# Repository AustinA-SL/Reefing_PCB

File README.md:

# Electronic Parachute Reefing PCB (Reef V3)

KiCad 10 project for the electronic parachute reefing controller.

- `V2_solenoid_removed/` is the V2 board (solenoid circuit removed, all parts on the top side). The original pre-V2 design is not tracked here.
- `libs/UL_Parts.pretty/` is a snapshot of the custom footprint library. The project's `fp-lib-table` still points at `C:/Users/austi/Documents/KiCad/10.0/footprints/UL_Parts.pretty`; footprints are also embedded in the `.kicad_pcb`, so the board opens without the library.

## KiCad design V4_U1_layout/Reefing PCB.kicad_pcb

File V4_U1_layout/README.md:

# Reef V3 controller — V4_U1_layout

Parachute reefing controller built around a Teensy 4.1. Four-layer board; every part is on the top side.

## Review files

| File | What it is |
|---|---|
| [plot/Reefing PCB schematic.pdf](plot/Reefing%20PCB%20schematic.pdf) | Full schematic |
| [docs/board_layers.pdf](docs/board_layers.pdf) | One page each: F.Cu, In1.Cu, In2.Cu, B.Cu, F.Silkscreen (with board outline) |
| [docs/board_top.png](docs/board_top.png) | 3D render, top side |
| [plot/](plot/) | Gerbers (`.gbr`, `.gbrjob`) and Excellon drill file (`.drl`) |

## Stackup

| Layer | Use |
|---|---|
| F.Cu | Components, signals, local power pours |
| In1.Cu | Solid GNDA plane |
| In2.Cu | Power: VIN and 12V pours, 24V and 3V3 routing |
| B.Cu | GNDA pour |

## Main parts

| Ref | Part | Function |
|---|---|---|
| U1 | TPS551892-Q1 | 12V buck-boost |
| U2 | TPS55340 | 24V boost |
| U3 | DRV8243-Q1 | Motor driver |
| U6 | LMR16006 | 5V buck |
| U8 / U9 | SN74LVC04 / SN74LVC10 | Interlock logic |
| IC1 | Teensy 4.1 | Controller |

## Net class track widths

| Class | Width |
|---|---|
| Power_4A | 1.5 mm |
| Motor | 1.0 mm |
| Power | 0.5 mm |
| Default | 0.2 mm |

## Fab notes

- Minimum drill is 0.2 mm (TI thermal-via patterns under U2 and U3).
- The U3 VM vias are in-pad and should be filled.
- The Teensy 4.1 footprint has its inner pads removed on purpose. Don't update that footprint from the library.
- DRC is clean as of 2026-11-16.

## Opening the design

1. Clone this repo.
2. Open `V4_U1_layout/Reefing PCB.kicad_pro` in KiCad 10.

The `UL_Parts` footprint library comes from `libs/UL_Parts.pretty` in this repo. All other footprints are stored inside the board file, so it opens and passes DRC without extra libraries.

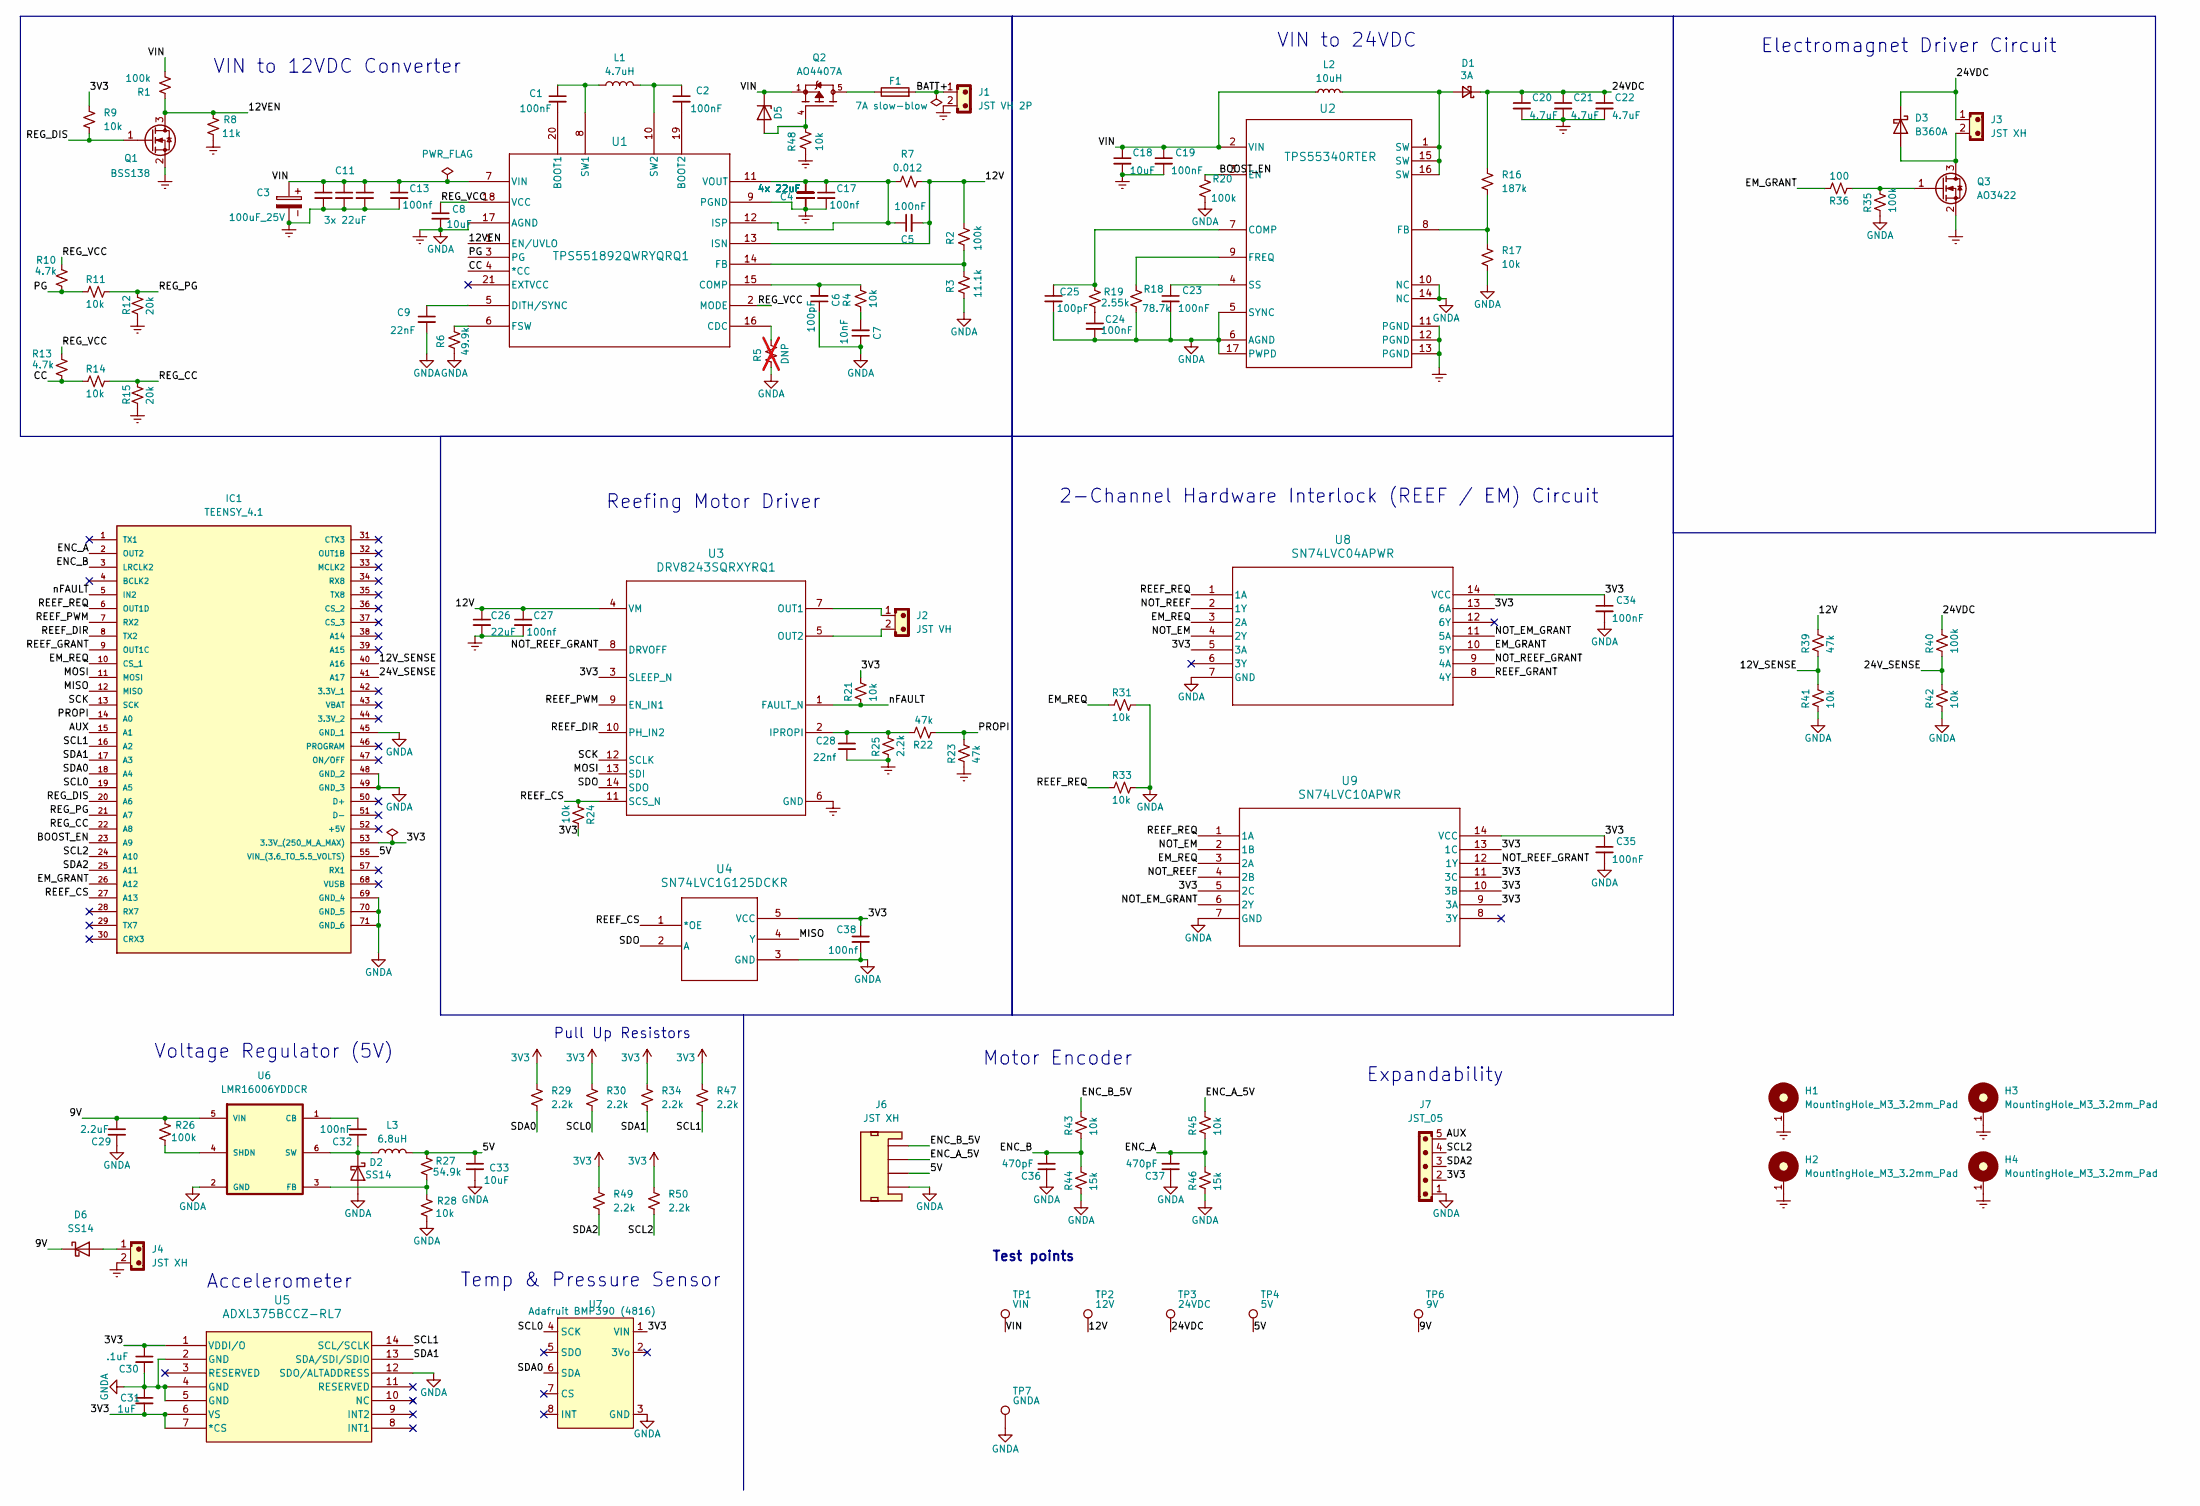
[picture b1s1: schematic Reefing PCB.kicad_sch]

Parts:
C1, C2: 100nF; C_0603_1608Metric; Voltage 10V; Tolerance 20%
C3: 100uF_25V; CP_Radial_D6.3mm_P2.50mm
C4, C14, C15, C16: 4x 22uF; C_1210_3225Metric; Voltage 25V; Tolerance 20%
C5, C19, C23, C24, C34, C35: 100nF; C_0603_1608Metric; Voltage 25V; Tolerance 20%
C6: 100pF; C_0603_1608Metric; Voltage 10V; Tolerance 20%
C7: 10nF; C_0603_1608Metric; Voltage 10V; Tolerance 20%
C8: 10uF; C_1206_3216Metric; Voltage 16V; Tolerance 20%
C9: 22nF; C_0603_1608Metric; Voltage 10V; Tolerance 20%
C10, C11, C12: 3x 22uF; C_1210_3225Metric; Voltage 50V; Tolerance 20%
C13, C17, C27: 100nf; C_0603_1608Metric; Voltage 25V; Tolerance 20%
C18: 10uF; C_1210_3225Metric; Voltage 50V; Tolerance 20%
C20, C21, C22: 4.7uF; C_1210_3225Metric; Voltage 50V; Tolerance 20%
C25: 100pF; C_0603_1608Metric; Voltage 25V; Tolerance 20%
C26: 22uF; C_1210_3225Metric; Voltage 50V; Tolerance 20%
C28: 22nf; C_0603_1608Metric; Voltage 10V; Tolerance 20%
C29: 2.2uF; C_0805_2012Metric
C30: .1uF; C_0603_1608Metric
C31: 1uF; C_0603_1608Metric
C32: 100nF; C_0603_1608Metric
C33: 10uF; C_0805_2012Metric
C36, C37: 470pF; C_0603_1608Metric
C38: 100nf; C_0603_1608Metric; Voltage 10V; Tolerance 20%
D1: SK34A; D_SMA
D2, D6: SS14; D_SMA
D3: B360A; D_SMA
D5: BZT52C15; D_SOD-123F
F1: 7A slow-blow; Fuse_Littelfuse-NANO2-451_453
H1, H2, H3, H4: MountingHole_M3_3.2mm_Pad; MountingHole_3.2mm_Pad
IC1: TEENSY_4.1; TEENSY41; Manufacturer_Part_Number TEENSY 4.1
J1: JST VH 2P; JST_VH_B2P-VH_1x02_P3.96mm_Vertical
J2: JST VH; JST_VH_B2P-VH_1x02_P3.96mm_Vertical
J3: JST XH; JST_GH_SM02B-GHS-TB_1x02-1MP_P1.25mm_Horizontal
J4: JST XH; JST_XH_B2B-XH-A_1x02_P2.50mm_Vertical
J6: JST XH; JST_GH_SM04B-GHS-TB_1x04-1MP_P1.25mm_Horizontal
J7: JST_05; JST_GH_SM05B-GHS-TB_1x05-1MP_P1.25mm_Horizontal
L1: 4.7uH; L_Coilcraft_XAL6060-XXX
L2: 10uH; L_Coilcraft_XAL4040-XXX
L3: 6.8uH; L_Coilcraft_LPS4018
Q1: BSS138; SOT-23
Q2: AO4407A; SOIC127P600X175-8N; PARTREV I
Q3: AO3422; SOT-23
R1, R2, R20, R26, R35, R40: 100k; R_0603_1608Metric
R3: 11.1k; R_0603_1608Metric
R4, R9, R11, R14, R17, R21, R24, R28, R31, R33, R41, R42, R43, R45, R48: 10k; R_0603_1608Metric
R5: DNP; R_0603_1608Metric; not fitted
R6: 49.9k; R_0603_1608Metric
R7: 0.012; R_2512_6332Metric
R8: 11k; R_0603_1608Metric
R10, R13: 4.7k; R_0603_1608Metric
R12, R15: 20k; R_0603_1608Metric
R16: 187k; R_0603_1608Metric
R18: 78.7k; R_0603_1608Metric
R19: 2.55k; R_0603_1608Metric
R22, R23, R39: 47k; R_0603_1608Metric
R25, R29, R30, R34, R47, R49, R50: 2.2k; R_0603_1608Metric
R27: 54.9k; R_0603_1608Metric
R36: 100; R_0603_1608Metric
R44, R46: 15k; R_0603_1608Metric
TP1: VIN; TestPoint_Pad_D1.5mm
TP2: 12V; TestPoint_Pad_D1.5mm
TP3: 24VDC; TestPoint_Pad_D1.5mm
TP4: 5V; TestPoint_Pad_D1.5mm
TP6: 9V; TestPoint_Pad_D1.5mm
TP7: GNDA; TestPoint_Pad_D1.5mm
U1: TPS551892QWRYQRQ1; VQFN21_RYQ_TEX
U2: TPS55340RTER; RTE0016C
U3: DRV8243SQRXYRQ1; RXY0014A-MFG
U4: SN74LVC1G125DCKR; DCK5
U5: ADXL375BCCZ-RL7; LGA_CC-14-1_ADI
U6: LMR16006YDDCR; SOT95P280X110-6N
U7: Adafruit BMP390 (4816); PinSocket_1x08_P2.54mm_Vertical
U8: SN74LVC04APWR; PW14
U9: SN74LVC10APWR; PW14

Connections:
3V3: C30.1, C31.2, C34.1, C35.1, C38.1, IC1.53 (3.3V_(250_M_A_MAX)), J7.2, R9.2, R21.1, R24.1, R29.2, R30.2, R34.2, R47.2, R49.2, R50.2, U3.3 (SLEEP_N), U4.5 (VCC), U5.1 (VDDI/O), U5.6 (VS), U5.7 (*CS), U7.1 (VIN), U8.5 (3A), U8.13 (6A), U8.14 (VCC), U9.5 (2C), U9.9 (3A), U9.10 (3B), U9.11 (3C), U9.13 (1C), U9.14 (VCC)
/5V: C33.1, IC1.55 (VIN_(3.6_TO_5.5_VOLTS)), J6.2, L3.2, R27.2, TP4.1 (1_1)
/9V: C29.1, D6.1 (K), R26.2, TP6.1 (1_1), U6.5 (VIN)
/12V: C5.2, C26.1, C27.1, R2.2, R7.2, R39.1, TP2.1 (1_1), U1.13 (ISN), U3.4 (VM)
/12VEN: Q1.3 (D), R1.2, R8.1, U1.1 (EN/UVLO)
/12V_SENSE: IC1.40 (A16), R39.2, R41.1
/24VDC: C20.1, C21.1, C22.1, D1.1 (K), D3.1 (K), J3.1, R16.2, R40.1, TP3.1 (1_1)
/24V_SENSE: IC1.41 (A17), R40.2, R42.1
/AUX: IC1.15 (A1), J7.5
/BATT+: F1.2, J1.1
/BOOST_EN: IC1.23 (A9), R20.2, U2.3 (EN)
/CC: R13.1, R14.2, U1.4 (*CC)
/EM_GRANT: IC1.26 (A12), R36.1, U8.10 (5Y)
/EM_REQ: IC1.10 (CS_1), R31.2, U8.3 (2A), U9.3 (2A)
/ENC_A: C37.1, IC1.2 (OUT2), R45.2, R46.1
/ENC_A_5V: J6.3, R45.1
/ENC_B: C36.1, IC1.3 (LRCLK2), R43.2, R44.1
/ENC_B_5V: J6.4, R43.1
/MISO: IC1.12 (MISO), U4.4 (Y)
/MOSI: IC1.11 (MOSI), U3.13 (SDI)
/NOT_EM: U8.4 (2Y), U9.2 (1B)
/NOT_EM_GRANT: U8.11 (5A), U9.6 (2Y)
/NOT_REEF: U8.2 (1Y), U9.4 (2B)
/NOT_REEF_GRANT: U3.8 (DRVOFF), U8.9 (4A), U9.12 (1Y)
/PG: R10.1, R11.2, U1.3 (PG)
/PROPI: IC1.14 (A0), R22.2, R23.1
/REEF_CS: IC1.27 (A13), R24.2, U3.11 (SCS_N), U4.1 (*OE)
/REEF_DIR: IC1.8 (TX2), U3.10 (PH_IN2)
/REEF_GRANT: IC1.9 (OUT1C), U8.8 (4Y)
/REEF_PWM: IC1.7 (RX2), U3.9 (EN_IN1)
/REEF_REQ: IC1.6 (OUT1D), R33.2, U8.1 (1A), U9.1 (1A)
/REG_CC: IC1.22 (A8), R14.1, R15.2
/REG_DIS: IC1.20 (A6), Q1.1 (G), R9.1
/REG_PG: IC1.21 (A7), R11.1, R12.2
/REG_VCC: C8.1, R10.2, R13.2, U1.2 (MODE), U1.18 (VCC)
/SCK: IC1.13 (SCK), U3.12 (SCLK)
/SCL0: IC1.19 (A5), R30.1, U7.4 (SCK)
/SCL1: IC1.16 (A2), R47.1, U5.14 (SCL/SCLK)
/SCL2: IC1.24 (A10), J7.4, R50.1
/SDA0: IC1.18 (A4), R29.1, U7.6 (SDA)
/SDA1: IC1.17 (A3), R34.1, U5.13 (SDA/SDI/SDIO)
/SDA2: IC1.25 (A11), J7.3, R49.1
/SDO: U3.14 (SDO), U4.2 (A)
/VIN: C3.1, C10.1, C11.1, C12.1, C13.1, C18.1, C19.1, D5.1 (K), L2.1, Q2.1, Q2.2, Q2.3, R1.1, TP1.1 (1_1), U1.7 (VIN), U2.2 (VIN)
/nFAULT: IC1.5 (IN2), R21.2, U3.1 (FAULT_N)
GNDA: C3.2, C4.2, C6.1, C7.1, C8.2, C9.2, C10.2, C11.2, C12.2, C13.2, C14.2, C15.2, C16.2, C17.2, C18.2, C19.2, C20.2, C21.2, C22.2, C23.2, C24.2, C25.2, C26.2, C27.2, C28.2, C29.2, C30.2, C31.1, C33.2, C34.2, C35.2, C36.2, C37.2, C38.2, D2.2 (A), H1.1, H2.1, H3.1, H4.1, IC1.45 (GND_1), IC1.48 (GND_2), IC1.49 (GND_3), IC1.69 (GND_4), IC1.70 (GND_5), IC1.71 (GND_6), J1.2, J4.2, J6.1, J7.1, Q1.2 (S), Q3.2 (S), R3.1, R5.1, R6.1, R8.2, R12.1, R15.1, R17.1, R18.1, R20.1, R23.2, R25.2, R28.1, R31.1, R33.1, R35.2, R41.2, R42.2, R44.2, R46.2, R48.1, TP7.1 (1_1), U1.9 (PGND), U1.17 (AGND), U2.5 (SYNC), U2.6 (AGND), U2.10 (NC), U2.11 (PGND), U2.12 (PGND), U2.13 (PGND), U2.14 (NC), U2.17 (PWPD), U3.6 (GND), U4.3 (GND), U5.2 (GND), U5.4 (GND), U5.5 (GND), U5.12 (SDO/ALTADDRESS), U6.2 (GND), U7.3 (GND), U8.7 (GND), U9.7 (GND)
unnamed: C7.2, R4.1
unnamed: C24.1, R19.1
unnamed: D1.2 (A), L2.2, U2.1 (SW), U2.15 (SW), U2.16 (SW)
unnamed: C32.2, D2.1 (K), L3.1, U6.6 (SW)
unnamed: D3.2 (A), J3.2, Q3.3 (D)
unnamed: D5.2 (A), Q2.4, R48.2
unnamed: D6.2 (A), J4.1
unnamed: F1.1, Q2.5, Q2.6, Q2.7, Q2.8
unnamed: Q3.1 (G), R35.1, R36.2
unnamed: C1.2, U1.20 (BOOT1)
unnamed: C2.2, U1.19 (BOOT2)
unnamed: R5.2, U1.16 (CDC)
unnamed: C6.2, R4.2, U1.15 (COMP)
unnamed: C9.1, U1.5 (DITH/SYNC)
unnamed: R2.1, R3.2, U1.14 (FB)
unnamed: R6.2, U1.6 (FSW)
unnamed: C4.1, C5.1, C14.1, C15.1, C16.1, C17.1, R7.1, U1.11 (VOUT), U1.12 (ISP)
unnamed: C1.1, L1.1, U1.8 (SW1)
unnamed: C2.1, L1.2, U1.10 (SW2)
unnamed: C25.1, R19.2, U2.7 (COMP)
unnamed: R16.1, R17.2, U2.8 (FB)
unnamed: R18.2, U2.9 (FREQ)
unnamed: C23.1, U2.4 (SS)
unnamed: C28.1, R22.1, R25.1, U3.2 (IPROPI)
unnamed: J2.1, U3.7 (OUT1)
unnamed: J2.2, U3.5 (OUT2)
unnamed: C32.1, U6.1 (CB)
unnamed: R27.1, R28.2, U6.3 (FB)
unnamed: R26.1, U6.4 (SHDN)

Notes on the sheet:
Pull Up Resistors
Reefing Motor Driver
VIN to 12VDC Converter
Expandability
Temp & Pressure Sensor
Electromagnet Driver Circuit
2-Channel Hardware Interlock (REEF / EM) Circuit
Accelerometer
VIN to 24VDC
Test points
Motor Encoder
Voltage Regulator (5V)

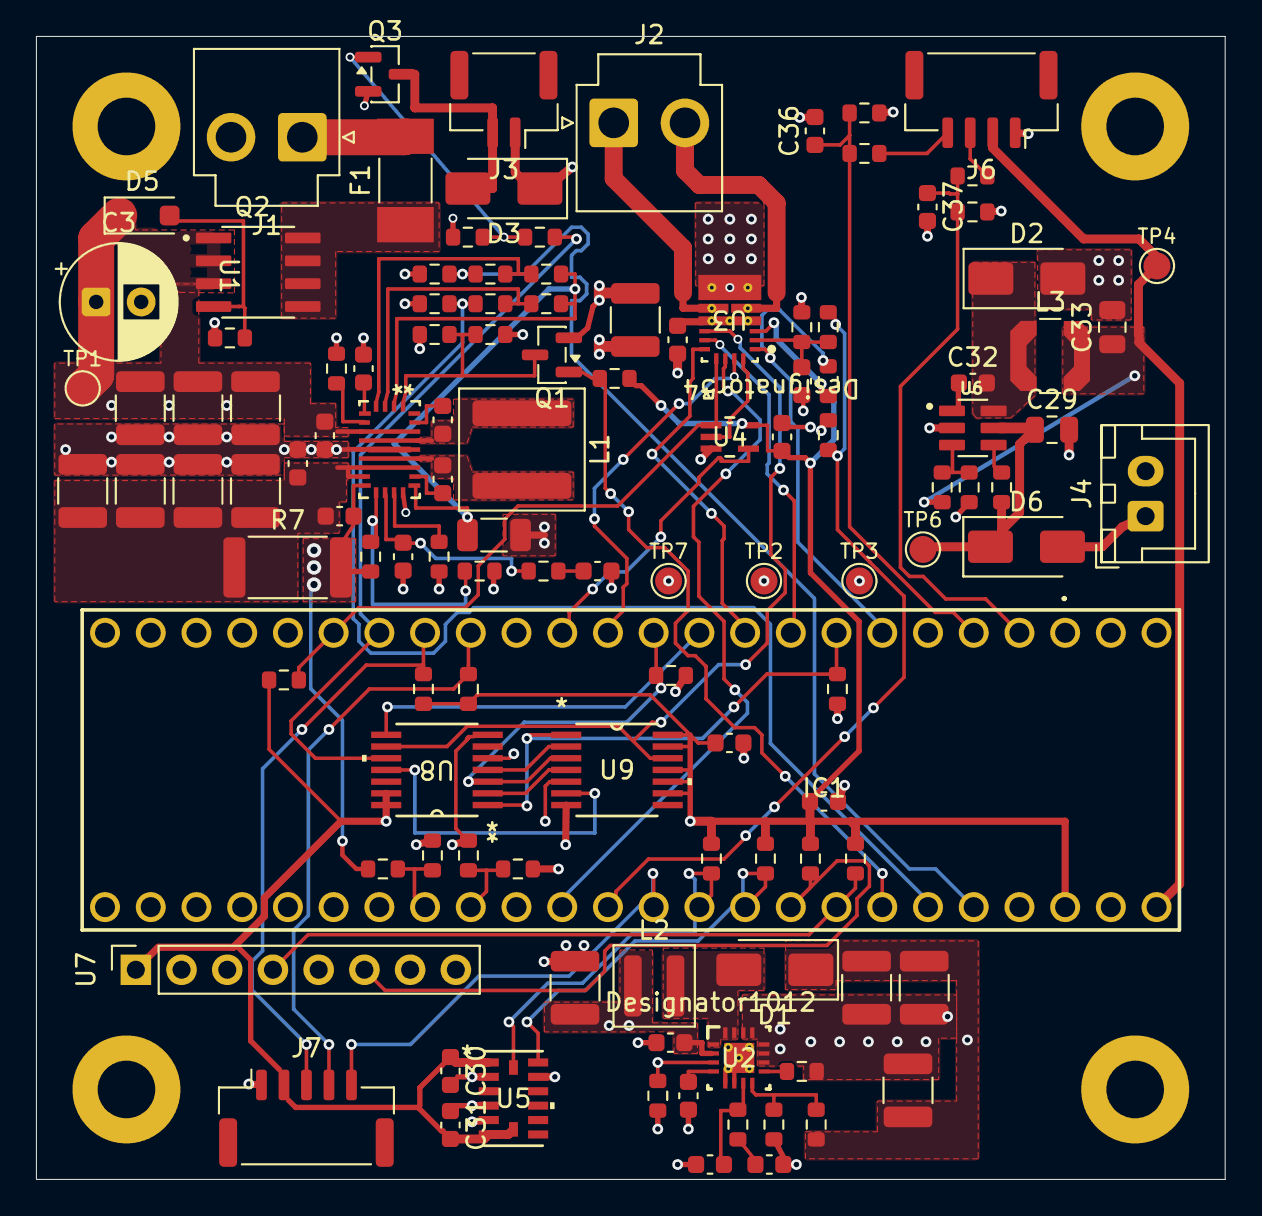
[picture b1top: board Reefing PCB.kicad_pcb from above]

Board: 4 copper layers, 66.0 x 63.5 mm, 123 parts (0 on the bottom side), 75 nets.
